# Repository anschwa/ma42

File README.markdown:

The MA42 Keyboard
=================

A programmable 42% mechanical keyboard for Dvorak.

Created by Michael Gobeli and Adam Schwartz.

With the help of:

- [jdcarpe](https://geekhack.org/index.php?action=profile;u=17386)
- [thechemist](https://geekhack.org/index.php?action=profile;u=27275)
- [geekhack.org](https://geekhack.org/index.php)

# Editor

[TMK Keymap Editor for MA42](http://anschwa.com/tmk_keyboard/editor/ma42/index.html).

Based on the [TMK Keymap Editor for the HHKB](http://www.tmk-kbd.com/tmk_keyboard/editor/hhkb/index.html).

# Photos

# License
The MA42 project is licensed under MIT unless otherwise noted.

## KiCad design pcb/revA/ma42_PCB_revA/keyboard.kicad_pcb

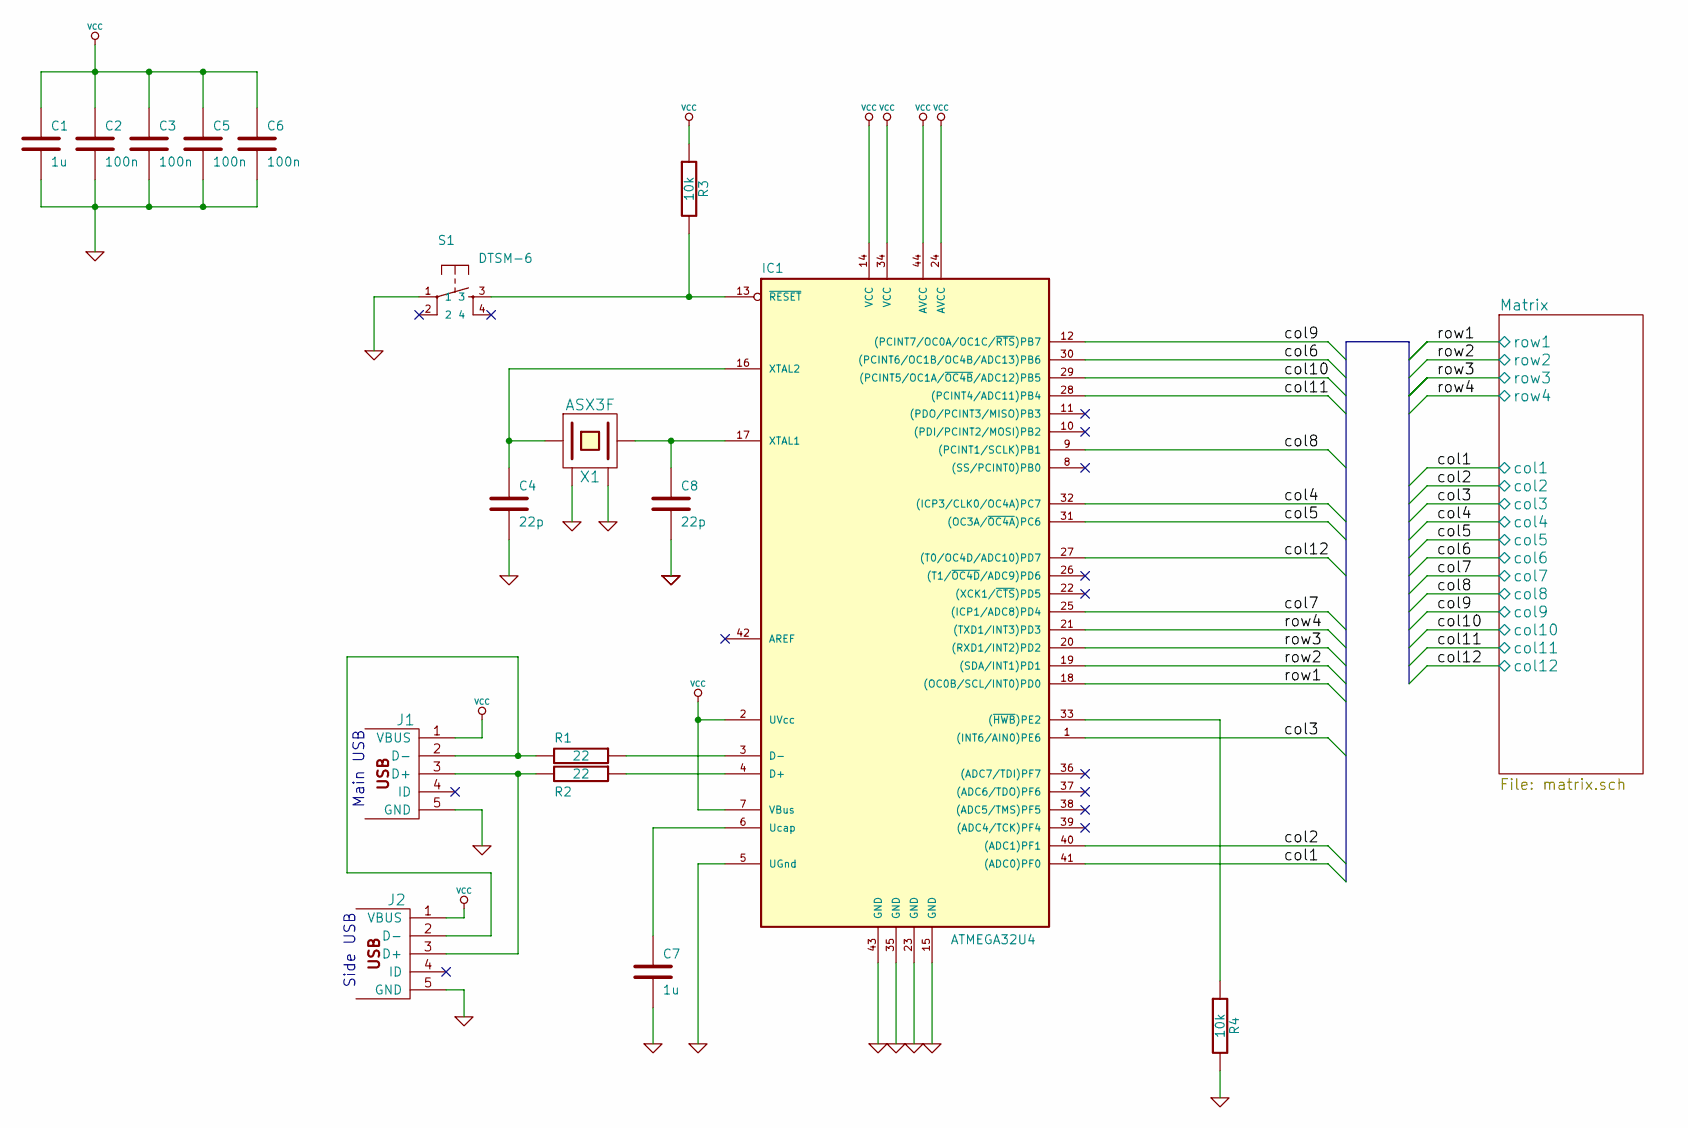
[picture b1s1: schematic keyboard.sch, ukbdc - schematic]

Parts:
C1, C7: 1u
C2, C3, C5, C6: 100n
C4, C8: 22p
IC1: ATMEGA32U4; TQFP44
J1: MINI
J2: USBMINI_B05
R1, R2: 22
R3, R4: 10k
S1: DTSM-6; switch-tact-DTSM-6
X1: ASX3F

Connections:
/Matrix/col1: IC1.41 ((ADC0)PF0); also elsewhere on the board
/Matrix/col2: IC1.40 ((ADC1)PF1); also elsewhere on the board
/Matrix/col3: IC1.1 ((INT6/AIN0)PE6); also elsewhere on the board
/Matrix/col4: IC1.32 ((ICP3/CLK0/OC4A)PC7); also elsewhere on the board
/Matrix/col5: IC1.31 ((OC3A/~OC4A~)PC6); also elsewhere on the board
/Matrix/col6: IC1.30 ((PCINT6/OC1B/OC4B/ADC13)PB6); also elsewhere on the board
/Matrix/col7: IC1.25 ((ICP1/ADC8)PD4); also elsewhere on the board
/Matrix/col8: IC1.9 ((PCINT1/SCLK)PB1); also elsewhere on the board
/Matrix/col9: IC1.12 ((PCINT7/OC0A/OC1C/~RTS~)PB7); also elsewhere on the board
/Matrix/col10: IC1.29 ((PCINT5/OC1A/~OC4B~/ADC12)PB5); also elsewhere on the board
/Matrix/col11: IC1.28 ((PCINT4/ADC11)PB4); also elsewhere on the board
/Matrix/col12: IC1.27 ((T0/OC4D/ADC10)PD7); also elsewhere on the board
/Matrix/row1: IC1.18 ((OC0B/SCL/INT0)PD0); also elsewhere on the board
/Matrix/row2: IC1.19 ((SDA/INT1)PD1); also elsewhere on the board
/Matrix/row3: IC1.20 ((RXD1/INT2)PD2); also elsewhere on the board
/Matrix/row4: IC1.21 ((TXD1/INT3)PD3); also elsewhere on the board
GND: C1.2, C2.2, C3.2, C4.2, C5.2, C6.2, C7.2, C8.2, IC1.5 (UGnd), IC1.15 (GND), IC1.23 (GND), IC1.35 (GND), IC1.43 (GND), J1.5 (GND), J2.5 (GND), R4.2, S1.1, X1.2 (GND), X1.4 (GND)
unnamed: IC1.33 ((~HWB~)PE2), R4.1
unnamed: C8.1, IC1.17 (XTAL1), X1.3 (2)
unnamed: J1.3 (D+), J2.3 (D+), R2.2
unnamed: J1.2 (D-), J2.2 (D-), R1.2
unnamed: C7.1, IC1.6 (Ucap)
unnamed: IC1.4 (D+), R2.1
unnamed: IC1.3 (D-), R1.1
unnamed: C4.1, IC1.16 (XTAL2), X1.1
unnamed: IC1.13 (~RESET~), R3.2, S1.3
VCC: C1.1, C2.1, C3.1, C5.1, C6.1, IC1.2 (UVcc), IC1.7 (VBus), IC1.14 (VCC), IC1.24 (AVCC), IC1.34 (VCC), IC1.44 (AVCC), J1.1 (VBUS), J2.1 (VBUS), R3.1

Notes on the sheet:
Side USB
Main USB

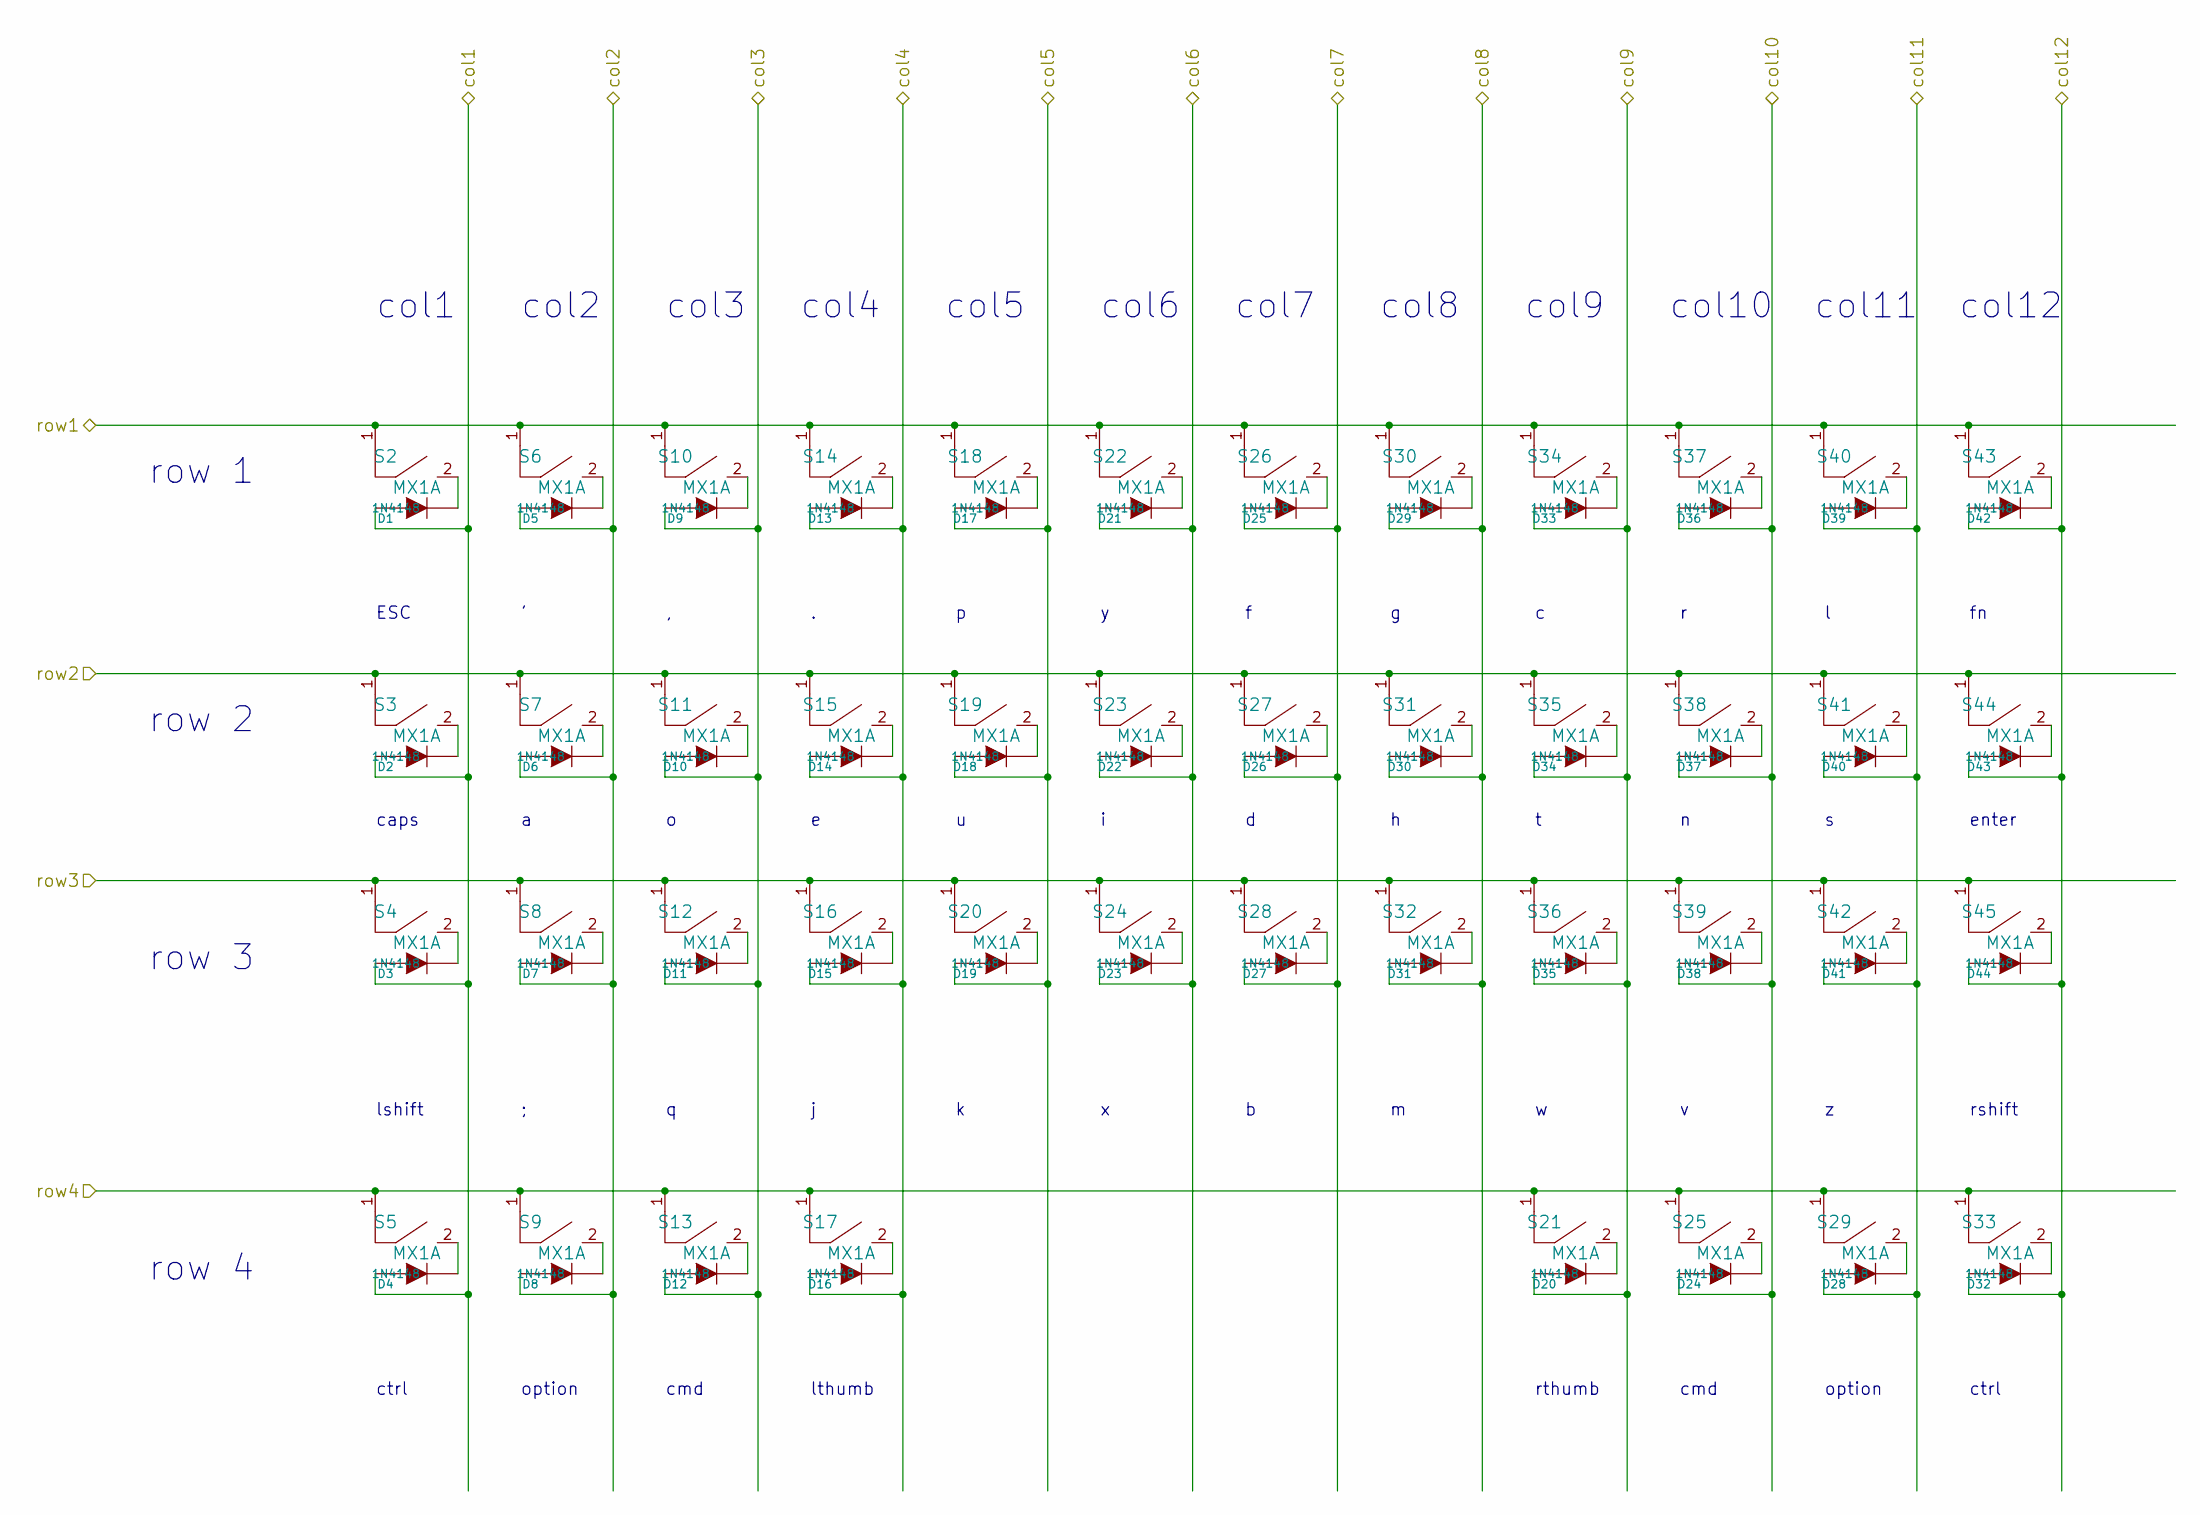
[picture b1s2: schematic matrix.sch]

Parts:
D1, D2, D3, D4, D5, D6, D7, D8, D9, D10, D11, D12, D13, D14, D15, D16, D17, D18, D19, D20, D21, D22, D23, D24, D25, D26, D27, D28, D29, D30, D31, D32, D33, D34, D35, D36, D37, D38, D39, D40, D41, D42, D43, D44: 1N4148
S2, S3, S4, S5, S6, S7, S8, S9, S10, S11, S12, S13, S14, S15, S16, S17, S18, S19, S20, S21, S22, S23, S24, S25, S26, S27, S28, S29, S30, S31, S32, S33, S34, S35, S36, S37, S38, S39, S40, S41, S42, S43, S44, S45: MX1A

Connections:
/Matrix/col1: D1.1 (A), D2.1 (A), D3.1 (A), D4.1 (A); also elsewhere on the board
/Matrix/col2: D5.1 (A), D6.1 (A), D7.1 (A), D8.1 (A); also elsewhere on the board
/Matrix/col3: D9.1 (A), D10.1 (A), D11.1 (A), D12.1 (A); also elsewhere on the board
/Matrix/col4: D13.1 (A), D14.1 (A), D15.1 (A), D16.1 (A); also elsewhere on the board
/Matrix/col5: D17.1 (A), D18.1 (A), D19.1 (A); also elsewhere on the board
/Matrix/col6: D21.1 (A), D22.1 (A), D23.1 (A); also elsewhere on the board
/Matrix/col7: D25.1 (A), D26.1 (A), D27.1 (A); also elsewhere on the board
/Matrix/col8: D29.1 (A), D30.1 (A), D31.1 (A); also elsewhere on the board
/Matrix/col9: D20.1 (A), D33.1 (A), D34.1 (A), D35.1 (A); also elsewhere on the board
/Matrix/col10: D24.1 (A), D36.1 (A), D37.1 (A), D38.1 (A); also elsewhere on the board
/Matrix/col11: D28.1 (A), D39.1 (A), D40.1 (A), D41.1 (A); also elsewhere on the board
/Matrix/col12: D32.1 (A), D42.1 (A), D43.1 (A), D44.1 (A); also elsewhere on the board
/Matrix/row1: S2.1, S6.1, S10.1, S14.1, S18.1, S22.1, S26.1, S30.1, S34.1, S37.1, S40.1, S43.1; also elsewhere on the board
/Matrix/row2: S3.1, S7.1, S11.1, S15.1, S19.1, S23.1, S27.1, S31.1, S35.1, S38.1, S41.1, S44.1; also elsewhere on the board
/Matrix/row3: S4.1, S8.1, S12.1, S16.1, S20.1, S24.1, S28.1, S32.1, S36.1, S39.1, S42.1, S45.1; also elsewhere on the board
/Matrix/row4: S5.1, S9.1, S13.1, S17.1, S21.1, S25.1, S29.1, S33.1; also elsewhere on the board
unnamed: D25.2 (K), S26.2
unnamed: D17.2 (K), S18.2
unnamed: D1.2 (K), S2.2
unnamed: D19.2 (K), S20.2
unnamed: D34.2 (K), S35.2
unnamed: D35.2 (K), S36.2
unnamed: D18.2 (K), S19.2
unnamed: D31.2 (K), S32.2
unnamed: D27.2 (K), S28.2
unnamed: D30.2 (K), S31.2
unnamed: D33.2 (K), S34.2
unnamed: D29.2 (K), S30.2
unnamed: D26.2 (K), S27.2
unnamed: D12.2 (K), S13.2
unnamed: D8.2 (K), S9.2
unnamed: D11.2 (K), S12.2
unnamed: D10.2 (K), S11.2
unnamed: D7.2 (K), S8.2
unnamed: D6.2 (K), S7.2
unnamed: D2.2 (K), S3.2
unnamed: D9.2 (K), S10.2
unnamed: D5.2 (K), S6.2
unnamed: D13.2 (K), S14.2
unnamed: D16.2 (K), S17.2
unnamed: D15.2 (K), S16.2
unnamed: D14.2 (K), S15.2
unnamed: D24.2 (K), S25.2
unnamed: D23.2 (K), S24.2
unnamed: D22.2 (K), S23.2
unnamed: D21.2 (K), S22.2
unnamed: D4.2 (K), S5.2
unnamed: D3.2 (K), S4.2
unnamed: D20.2 (K), S21.2
unnamed: D42.2 (K), S43.2
unnamed: D43.2 (K), S44.2
unnamed: D41.2 (K), S42.2
unnamed: D44.2 (K), S45.2
unnamed: D38.2 (K), S39.2
unnamed: D40.2 (K), S41.2
unnamed: D39.2 (K), S40.2
unnamed: D37.2 (K), S38.2
unnamed: D36.2 (K), S37.2
unnamed: D32.2 (K), S33.2
unnamed: D28.2 (K), S29.2

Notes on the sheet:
row 1
row 2
row 3
row 4
col1
col2
col3
col4
col5
col6
col7
col9
col10
col11
col12
col8
ESC
caps
enter
rshift
ctrl
option
cmd
lthumb
rthumb
lshift

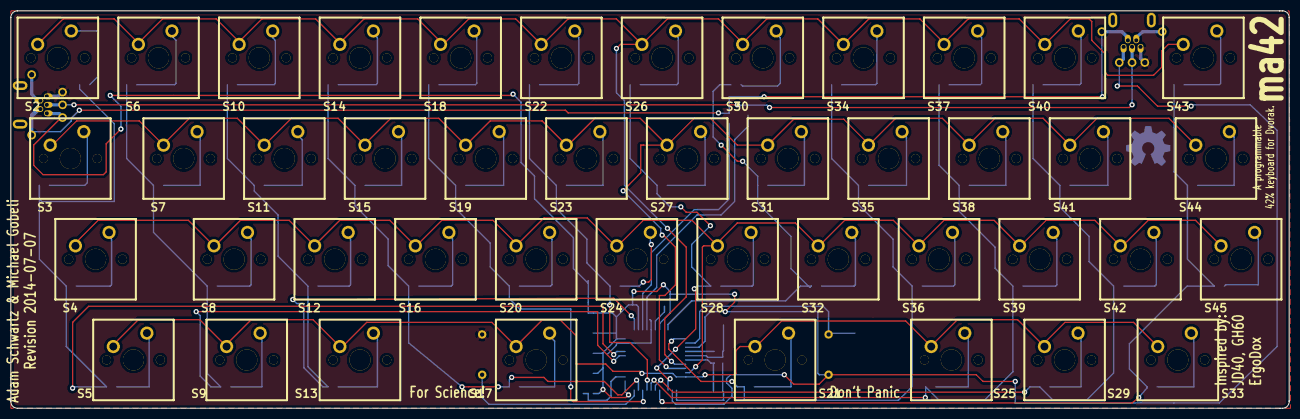
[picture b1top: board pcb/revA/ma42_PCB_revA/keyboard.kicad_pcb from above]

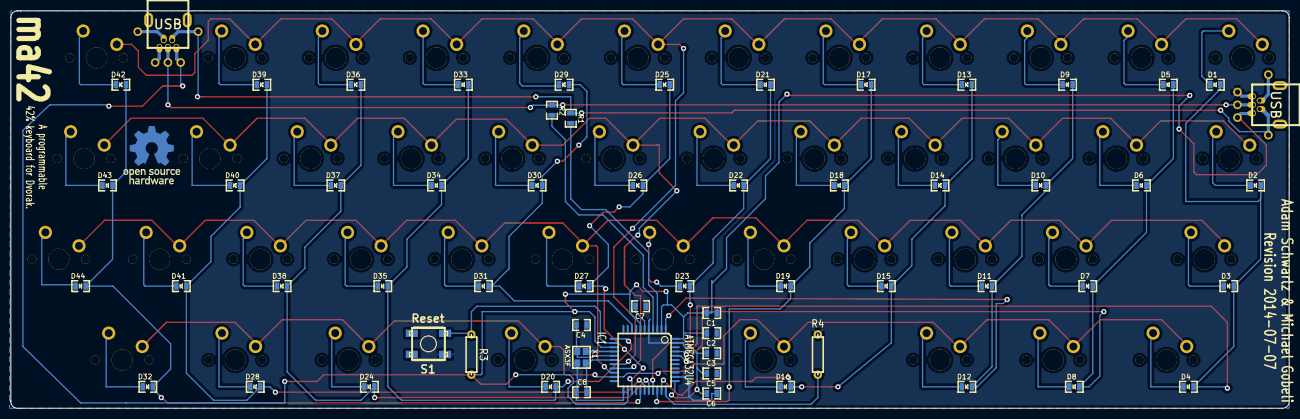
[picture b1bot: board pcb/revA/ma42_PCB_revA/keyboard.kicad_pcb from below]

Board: 2 copper layers, 241.8 x 75.2 mm, 105 parts (61 on the bottom side), 71 nets.

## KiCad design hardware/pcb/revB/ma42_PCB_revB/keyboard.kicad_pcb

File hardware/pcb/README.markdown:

The MA42 PCB
============

The MA42 PCBs are licensed under [CC BY-SA 3.0](https://creativecommons.org/licenses/by-sa/3.0/us/).

However, this is due to a misunderstanding with the `GH60` licensing.

The `GH60` KiCad Source we accesed in July 2014 was distributed as "open source" without any explicit licence.

- [gh60 downloads 2014](https://web.archive.org/web/20140701221151/http://blog.komar.be/projects/gh60-programmable-keyboard/)

Currently, the `GH60` download page was updated with a `CC BY-SA 3.0` license sometime after October 17 2014 Many months after our projects completion.

- [gh60 downloads 2015+](http://blog.komar.be/projects/gh60-programmable-keyboard/)

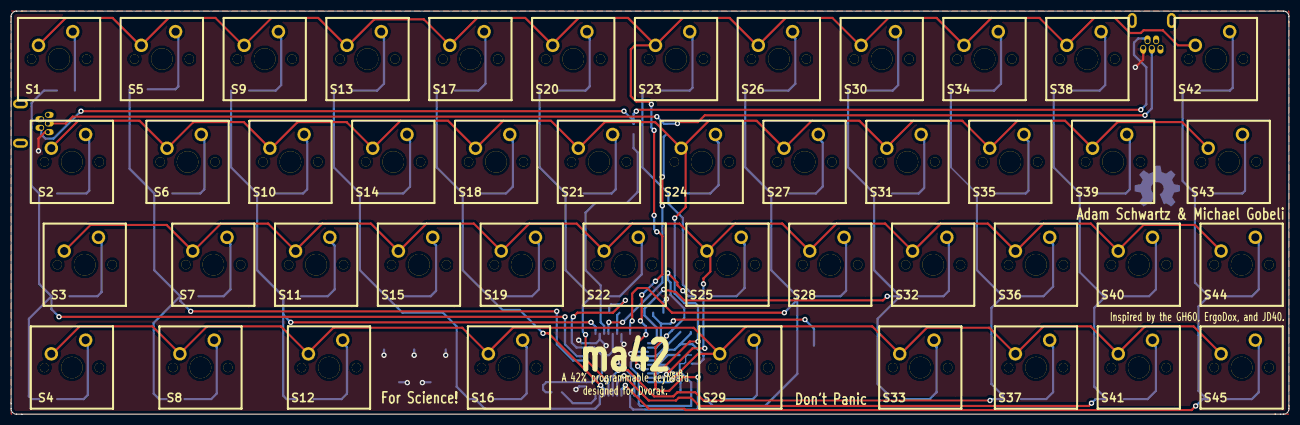
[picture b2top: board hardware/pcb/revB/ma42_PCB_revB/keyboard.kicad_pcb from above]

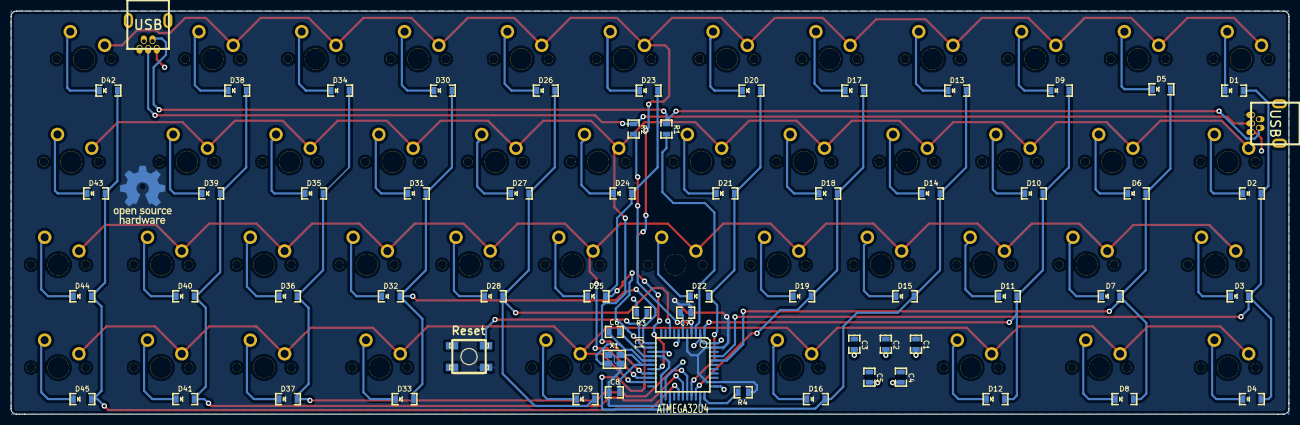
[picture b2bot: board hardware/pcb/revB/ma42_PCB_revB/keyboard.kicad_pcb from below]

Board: 2 copper layers, 236.7 x 74.7 mm, 107 parts (62 on the bottom side), 72 nets.

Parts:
C1, C7: 1u; SM0805
C2, C3, C4, C5: 100n; SM0805
C6, C8: 22p; SM0805
D1, D2, D3, D4, D5, D6, D7, D8, D9, D10, D11, D12, D13, D14, D15, D16, D17, D18, D19, D20, D21, D22, D23, D24, D25, D26, D27, D28, D29, D30, D31, D32, D33, D34, D35, D36, D37, D38, D39, D40, D41, D42, D43, D44, D45: 1N4148; SM0805D_big
IC1: ATMEGA32U4; TQFP44
J1, J2: USB; USBMINImod_small
R1, R2: 22; SM0805
R3, R4: 10k; SM0805
S1, S2, S3, S4, S5, S6, S7, S8, S9, S10, S11, S12, S13, S14, S15, S16, S17, S18, S19, S20, S21, S22, S23, S24, S25, S26, S27, S28, S29, S30, S31, S32, S33, S34, S35, S36, S37, S38, S39, S40, S41, S42, S43, S44, S45: MX1A; MX1A-b
S46: Reset; DTSJW-66N
X1: ASX3F

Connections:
/Matrix/col1: D1.1, D2.1, D3.1, D4.1, IC1.41
/Matrix/col2: D5.1, D6.1, D7.1, D8.1, IC1.40
/Matrix/col3: D9.1, D10.1, D11.1, D12.1, IC1.1
/Matrix/col4: D13.1, D14.1, D15.1, D16.1, IC1.32
/Matrix/col5: D17.1, D18.1, D19.1, IC1.31
/Matrix/col6: D20.1, D21.1, D22.1, IC1.30
/Matrix/col7: D23.1, D24.1, D25.1, IC1.25
/Matrix/col8: D26.1, D27.1, D28.1, D29.1, IC1.9
/Matrix/col9: D30.1, D31.1, D32.1, D33.1, IC1.12
/Matrix/col10: D34.1, D35.1, D36.1, D37.1, IC1.29
/Matrix/col11: D38.1, D39.1, D40.1, D41.1, IC1.28
/Matrix/col12: D42.1, D43.1, D44.1, D45.1, IC1.27
/Matrix/row1: IC1.18, S1.1, S5.1, S9.1, S13.1, S17.1, S20.1, S23.1, S26.1, S30.1, S34.1, S38.1, S42.1
/Matrix/row2: IC1.19, S2.1, S6.1, S10.1, S14.1, S18.1, S21.1, S24.1, S27.1, S31.1, S35.1, S39.1, S43.1
/Matrix/row3: IC1.20, S3.1, S7.1, S11.1, S15.1, S19.1, S22.1, S25.1, S28.1, S32.1, S36.1, S40.1, S44.1
/Matrix/row4: IC1.21, S4.1, S8.1, S12.1, S16.1, S29.1, S33.1, S37.1, S41.1, S45.1
GND: C1.2, C2.2, C3.2, C4.2, C5.2, C6.2, C7.2, C8.2, IC1.5, IC1.15, IC1.23, IC1.35, IC1.43, J1.5, J2.5, R4.2, S46.1, X1.2, X1.4
unnamed: IC1.33, R4.1
unnamed: J1.3, J2.3, R2.2
unnamed: IC1.13, R3.2, S46.3
unnamed: J1.2, J2.2, R1.2
unnamed: C7.1, IC1.6
unnamed: IC1.4, R2.1
unnamed: IC1.3, R1.1
unnamed: C6.1, IC1.16, X1.1
unnamed: C8.1, IC1.17, X1.3
unnamed: D19.2, S19.2
unnamed: D1.2, S1.2
unnamed: D26.2, S26.2
unnamed: D25.2, S25.2
unnamed: D24.2, S24.2
unnamed: D23.2, S23.2
unnamed: D17.2, S17.2
unnamed: D38.2, S38.2
unnamed: D35.2, S35.2
unnamed: D34.2, S34.2
unnamed: D31.2, S31.2
unnamed: D32.2, S32.2
unnamed: D18.2, S18.2
unnamed: D28.2, S28.2
unnamed: D27.2, S27.2
unnamed: D30.2, S30.2
unnamed: D20.2, S20.2
unnamed: D12.2, S12.2
unnamed: D8.2, S8.2
unnamed: D11.2, S11.2
unnamed: D21.2, S21.2
unnamed: D10.2, S10.2
unnamed: D7.2, S7.2
unnamed: D6.2, S6.2
unnamed: D2.2, S2.2
unnamed: D16.2, S16.2
unnamed: D15.2, S15.2
unnamed: D14.2, S14.2
unnamed: D13.2, S13.2
unnamed: D37.2, S37.2
unnamed: D22.2, S22.2
unnamed: D4.2, S4.2
unnamed: D3.2, S3.2
unnamed: D29.2, S29.2
unnamed: D45.2, S45.2
unnamed: D41.2, S41.2
unnamed: D33.2, S33.2
unnamed: D42.2, S42.2
unnamed: D43.2, S43.2
unnamed: D40.2, S40.2
unnamed: D44.2, S44.2
unnamed: D36.2, S36.2
unnamed: D39.2, S39.2
unnamed: D9.2, S9.2
unnamed: D5.2, S5.2
VCC: C1.1, C2.1, C3.1, C4.1, C5.1, IC1.2, IC1.7, IC1.14, IC1.24, IC1.34, IC1.44, J1.1, J2.1, R3.1

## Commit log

2014-06-09 made better layout template
2014-06-10 new layouts
2014-06-10 add new layout
2014-07-13 modified parts list
2014-07-13 add price.txt
2014-07-13 add pcb
2014-07-21 added revA and started work on revB PCB
2014-07-21 add Case / Plate
2014-07-21 update layout for revB
2014-07-29 working on revB
2014-07-29 add revB PCB and Case
2014-08-29 various project file updates
2014-10-18 cleanup revB files
2015-01-01 separate into 'hardware' and 'software' directories
2015-05-19 cleanup hardware/ and provide working firmware hex
    add sample ma42_firmware.hex
    update software/setup.markdown
    add software/resources.markdown
    remove remaining .DS_Store files
    remove cache of software/inpiration/tmk_keyboard
    reorganize revA pcb archives
2015-05-19 add my tmk_keyboard fork as a submodule
2015-05-19 update project readme
    add pcb readme
2015-05-20 update gitignore
2015-05-20 update readme to include link to editor
2015-05-20 add photos directory
2017-06-10 update bom
2021-11-30 add photo of pcb to readme
